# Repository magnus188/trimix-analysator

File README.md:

# Trimix Analyzer ESP32 Firmware

ESP32-P4/LVGL firmware for the Trimix Analyzer on the native-portrait Guition JC4880P443C_I_W (JC-ESP32P4-M3). It includes Wi-Fi, revision-specific HTTPS OTA, persistent settings/calibration, hardware sensor and power drivers, and a separate deterministic simulator. Physical firmware reports unavailable hardware instead of substituting simulated gas or battery readings.

**Prototype order status: HOLD.** Follow the [whole-system review](hardware/system-review/README.md) for current evidence and unresolved interfaces. No physical charging, thermal, sealing or reference-gas qualification has been completed. The accuracy targets of ±0.2 percentage points O2 and ±0.5 points He remain unproven. Charging is deliberately inhibited and J104 stays open until the cell, protection and temperature-sensing requirements are qualified.

## Project layout

The repository root is the main software workspace: firmware lives in `main/`,
with host tests in `tests/`, simulator support in `simulator/` and development
tools in `scripts/`. Mechanical and electronics files are grouped under the
[hardware overview](hardware/README.md): Fusion CAD is in `hardware/cad/`,
KiCad PCB projects are in `hardware/pcb/`, and Bambu Studio projects are in
`hardware/cad/rev04/3d-print/printing/bambu-studio/`.

## Quick Start with ESP-IDF

### Prerequisites
- [ESP-IDF v5.5.4](https://github.com/espressif/esp-idf/releases/tag/v5.5.4); `make setup-idf` installs the pinned environment
- Python 3.13
- Guition JC4880P443C_I_W: ESP32-P4 rev v1.3, 16 MB flash, 32 MB PSRAM, and ESP32-C6 coprocessor
- `g++`, CMake, pkg-config, and SDL2 development headers for full host validation

### Build and Upload
```bash
# See all common development commands
make help

# Run host-side validation
make test

# Install/check the exact ESP-IDF toolchain
make setup-idf
make doctor

# Identify whether the attached P4 is pre-v3 or v3+
make board-info PORT=/dev/cu.usbserial-110

# Build and flash; the port is required so the revision can be verified safely
make push PORT=/dev/cu.usbserial-110

# Build, flash, and monitor serial output
make push-monitor PORT=/dev/cu.usbserial-110

# Build and run the LVGL/SDL desktop simulator
make sim ZOOM=0.75
```

The first ESP32-P4 installation must be flashed over USB. An ESP32-S3 cannot
install this firmware through OTA because the chips and images are incompatible.

Run `make devices` to find likely serial ports. Firmware commands always source the pinned ESP-IDF v5.5.4 installation under `~/esp/v5.5.4/esp-idf`; an unrelated `idf.py` in `PATH` is never used. Override the installation location with `ESP_IDF_DIR=/path/to/esp-idf`.

The equivalent raw ESP-IDF commands remain available:

```bash
idf.py -B build/esp32p4-pre3 -D SDKCONFIG_DEFAULTS="sdkconfig.defaults;sdkconfig.defaults.esp32p4;sdkconfig.defaults.esp32p4.pre3" set-target esp32p4
idf.py -B build/esp32p4-pre3 build
idf.py -B build/esp32p4-pre3 -p /dev/cu.usbserial-110 flash monitor
```

## Browser Demo

The production LVGL interface can also run in a browser through WebAssembly. The browser build uses the same screens, calculator logic, and deterministic simulator services as the native SDL simulator; hardware sensors, WiFi, battery state, NVS, and OTA installation remain simulated.

### Build locally

Activate an [Emscripten SDK](https://emscripten.org/docs/getting_started/downloads.html), then run:

```bash
bash scripts/build_web_demo.sh
python3 -m http.server 8080 --directory web/build
```

Open `http://localhost:8080`. The generated site must be served over HTTP rather than opened directly from disk so the browser can load its WebAssembly module.

### Automatic GitHub Pages deployment

`.github/workflows/pages.yml` builds and deploys the demo after every push to `main`, and can also be run manually. Before the first deployment, select **GitHub Actions** under **Repository settings → Pages → Build and deployment → Source**. The project site will then be available at `https://magnus188.github.io/trimix-analysator/`.

### ESP-IDF Project Structure
```
├── CMakeLists.txt           # Main CMake configuration
├── sdkconfig.defaults       # ESP-IDF configuration defaults
├── main/                    # Main component source files
│   ├── main.cpp            # Application entry point and service startup
│   ├── services/           # WiFi, OTA, settings, battery, backlight
│   ├── sensors/            # Sensor abstraction and mock readings
│   ├── ui/                 # LVGL port, screens, styles, components
│   ├── idf_component.yml  # Component dependencies
│   └── CMakeLists.txt     # Component CMake file
├── tests/                  # Host-side C++ tests
├── scripts/                # Test and firmware size scripts
└── README.md               # This file
```

## Hardware Requirements

Use the [current electrical design](hardware/ANALYZER_DESIGN.md), [part qualification ledger](hardware/system-review/electrical/part-qualification.csv) and [main-board delivery index](hardware/system-review/electrical/main-final/README.md). These are prototype review files, not purchasing approval. Earlier enclosure/PCB snapshots preserve historical component choices.

### Controller and Display
- **ESP32-P4NRW32** application processor with 32 MB in-package PSRAM. Original pre-v3 boards are configured for their detected 16 MB flash; the v3 profile retains the 32 MB layout used by newer hardware.
- Onboard **ESP32-C6** WiFi 6/BLE coprocessor connected over SDIO.
- Native **480x800 MIPI-DSI IPS display** with ST7701 controller and GT911 capacitive touch.

### Power, Charging, and Battery
- **GCT USB4720-03-A** on a separate thin USB board, with TUSB320LAI CC detection and PI3USB9201 BC1.2 detection on the main board. USB-A-to-C and C-to-C behaviour remains subject to the documented source-current and startup tests.
- **BQ25895RTWR** 1S power-path charger, with TPS259470 overvoltage protection and TPS22950-Q1 input limiting. No USB-PD or high-voltage negotiation is provided; charging remains inhibited during commissioning.
- **Protected FMA FPML1S2P050C holder**, using its protected output. Holder/protection ratings, cell identity and NTC mounting require qualification.
- **TPS63020** configured for 5 V, with LM66100 host reverse isolation. Guition JP1 power entry remains a separate unresolved interface; do not power it through an unqualified harness.
- **TPS7A2030** regulated 3.0 V supply for the MD62.
- **LTC2954** hardware push-button shutdown plus firmware-managed normal shutdown.
- **MAX17048** 1S I2C fuel gauge.
- **2x 18650 cells in 1S2P**, owner-stated 3400 mAh each; no validated cell charge limits are inferred from capacity.
- **Normally-open momentary power button**; its final mechanical part and sealing remain unqualified.

### Sensors and Analog Front End
- Two **ADS122C04IPWR** 24-bit ADCs in TSSOP-16: U401 oxygen at 0x40 and U502 helium at 0x41. Initial profiles use 20 samples/s and the internal 2.048 V reference.
- Actual **BME280** breakout for humidity, temperature and pressure. A BMP280 cannot provide humidity.
- Retained **MD62 thermal-conductivity sensor** on regulated 3.0 V, with fixed matched bridge reference. Its helium response and compensation must be characterized with reference mixtures.
- **AO2 or R17JJ-CCR**, one installed oxygen sensor at a time. J401 and J402 have separate differential inputs; touchscreen selection and calibration identities persist independently.
- **ZE07-CO experimental module**, measuring CO rather than CO2. It is not a breathing-gas safety certification device. Its manufacturer excludes applications involving human safety; see the [CO review and manual](hardware/system-review/electrical/co-module-use-review.md). No undocumented recalibration commands are enabled. Fresh, valid chamber conditions and module warm-up are required before its reading is displayed.

### Wiring Notes
```
Signal/Rail       | Current hardware expectation
------------------|------------------------------------------------
External I2C      | GPIO28 SDA / GPIO29 SCL; managed 100 kHz sensor/power bus
Analog gas inputs | AO2/JJ differential paths and MD62 bridge into ADS122C04
HOST_3V3          | Supplied by Guition; external load margin remains unqualified
3.0 V rail        | MD62 through TPS7A2030; measure voltage at actual sensor leads
USB-C VBUS        | Protected/limited 5 V path to BQ25895
Display I2C       | GPIO7 SDA / GPIO8 SCL; separate touch/audio board bus
Onboard SD        | Slot 0: CLK43 CMD44 D0-3=39-42; LDO4 card supply
C6 SDIO           | Slot 1: CLK18 CMD19 D0-3=14-17; shared-controller arbitration
```

The [electrical/firmware/harness contract](hardware/system-review/electrical/interface-contract.md) defines logical contact mapping. The [owner photo and mechanical registration](hardware/system-review/integration-photo/README.md) place the Guition header and both USB sockets at the top and SD access on the left. Mated connector heights, cable routes and service access need their own clearance evidence. Display pins, timings and the ST7701S initialization table live in `main/board/`.

## Software Architecture

### Key Components

#### 1. Main Application (`main/main.cpp`)
- Persistent service startup
- Native display and screen initialization under the LVGL adapter lock
- Background service startup after the UI is ready

#### 2. LVGL Port (`main/ui/lvgl/lvgl_port.cpp`)
- Guition MIPI-DSI/ST7701S manual startup sequence
- Native GT911 touch registration
- Triple-buffered tear avoidance and LVGL adapter locking

#### 3. Sensor Interface (`main/sensors/sensor_interface.cpp/h`)
- Abstracted sensor reading functions
- Separate physical acquisition and deterministic simulator backends
- Persistent sensor selection and versioned calibration; stale, clipped and faulty samples are rejected

#### 4. Screen Management (`main/ui/screens/screen_manager.cpp/h`)
- LVGL-based UI screens
- Navigation between screens
- Settings, WiFi, update, and dive planner screens

#### 5. Services (`main/services/`)
- WiFi scanning/connection and saved credentials
- OTA update checks and firmware installation
- Settings, battery status, and backlight control
- Analysis history, persistent cylinder profiles, and export-ready gas label payloads

#### 6. Board Support
- In-tree Guition JC4880P443 display, backlight, and touch layer
- Separate pre-v3 and v3+ ESP32-P4 build profiles
- Native backlight, display, touch, and onboard ESP32-C6 integration

## Display Configuration

### ESP32-P4 Display
- **Panel**: 480x800 native portrait
- **Framework**: LVGL
- **Touch**: Capacitive (GT911)

### Screens

1. **Home Screen**
   - Main menu with navigation buttons
   - System status display
   - Version information

2. **Analyse Screen**
   - Gas analysis panel with physical and separately identified simulator sources
   - O2, He, experimental CO, environmental readings, stability, trend chart, planned depth, MOD, density, gas-use mode and averaged capture controls
   - Captures require stable samples and save an averaged analysis result to history
   - Stable averaged readings can update the selected cylinder profile and prepare an export-ready label payload

3. **Dive Planner Screen**
   - Gas planning calculator views
   - Partial-pressure top-up calculator for O2, helium, and air additions
   - Production calculator logic covered by host tests

4. **History Screen**
   - Captured analysis records with gas-use mode, mix fractions, CO, planned depth, MOD, density and advisory state; legacy CO2 fields remain distinct and are not relabelled as CO

5. **Cylinder Profiles Screen**
   - Persistent cylinder slots with selected cylinder, recheck state, stored mix, gas-use mode, planned depth, and label preview
   - Label text and CSV payloads are generated in firmware so later WiFi, QR, BLE, or phone handoff export can reuse the same data model

6. **Settings Screen**
   - Device settings navigation
   - Cylinder profiles, WiFi, software update, safety settings, calibration, and device information entrypoints

7. **WiFi Screen**
   - Network scanning, connection, password modal, and disconnect controls

8. **Software Update Screen**
   - GitHub release check and OTA install flow

9. **Calibrate Sensors Screen**
   - Guided known-gas oxygen and helium calibration with stability/fault checks and separate AO2/JJ/He records; failed saves retain the previous calibration

10. **Safety Settings Screen**
   - User-configured PPO2, density, and CO2 advisory limits used by Analyse

11. **Device Screen**
   - Device information and configuration controls

## Building and Flashing

### Prerequisites
- **ESP-IDF v5.5.4** installed with `make setup-idf`
- **ESP32-P4** toolchain and Python 3.13
- **Host validation tools**: `g++`, CMake, pkg-config, SDL2 development headers
- USB-C cable for programming

### Build Steps
```bash
# Inspect the attached chip and select the safe image family
make board-info PORT=/dev/cu.usbserial-110

# Run host tests
./scripts/run_tests.sh

# Build both incompatible P4 revision profiles
make build-all

# Validate firmware size against partitions.csv
make size-check P4_REV=pre3
make size-check P4_REV=v3

# Flash to device
make push PORT=/dev/cu.usbserial-110

# Monitor output
make monitor PORT=/dev/cu.usbserial-110
```

### Dependencies
The project uses ESP-IDF component manager for dependencies (defined in `main/idf_component.yml`):
- `lvgl/lvgl` 9.4.0 - Graphics library
- `espressif/esp_lcd_touch_gt911` 1.2.x - capacitive touch controller
- `espressif/esp_lvgl_adapter` 0.1.4 - task, input, and tear-safe display integration
- `espressif/esp_wifi_remote` 1.6.0 and `espressif/esp_hosted` 2.12.9 - onboard C6 networking

Dependencies are automatically downloaded during the build process.

## Sensor Hardware and Calibration Status

Physical firmware implements ADS122C04 acquisition, environmental and power monitoring, sensor selection and calibration persistence. Host tests exercise faults and state transitions; they do not establish actual sensor performance, wiring or charging behaviour. The simulator remains explicitly identified and does not substitute readings in physical firmware.

AO2, JJ-CCR and helium have separate records. Replacing a sensor requires calibration. Helium corrections must come from measured reference mixtures and held-out validation, including environmental and oxygen cross-effects. Historical/simulated CO2 fields remain distinct; this build has no installed CO2 measurement module. See the [software review](hardware/system-review/software/README.md).

## Performance Characteristics

### Display Pipeline
- **Panel**: native 480x800 RGB565 over two-lane MIPI-DSI
- **Tear avoidance**: three full panel framebuffers with partial LVGL rendering
- **LVGL refresh period**: 15 ms
- **Rotation**: none; pixels and touch coordinates stay in native portrait orientation

### Power Consumption
Whole-device active, idle, charging and hardware-off consumption remains unmeasured. Qualify backlight, radio, SD writes, heaters, converters and cable losses together; a display-only typical value is not a system budget. See the [bench equipment and test plan](hardware/system-review/lab-equipment.md).

## Differences from Original

### Enhanced Features
1. **480x800 portrait touch display**
2. **Capacitive touch**
3. **Tear-safe MIPI-DSI output** with no full-frame software rotation
4. **Software-defined sensor selection and calibration**
5. **Versioned OTA and persistent storage**; boot-time and power comparisons remain unmeasured

### Current Limitations
1. Physical fit, source protection, cell charging, thermal behaviour and gas accuracy remain unqualified; PCB order readiness is on hold.
2. Simulator streams support repeatable UI/logic tests; they are not physical measurement evidence.
3. Settings, calibration and recent history remain in NVS. [Optional onboard SD logging](hardware/system-review/software/sd-card/README.md) automatically records analysis/calibration sessions, raw samples and events. Device Settings provides status, safe eject and retry. Digital tests pass; actual card operation, power loss and simultaneous Wi-Fi use remain untested. Absent or faulty media leaves local analysis available.

## Development Notes

### Code Organization
- Sensor interface abstraction allows host tests and later hardware drivers.
- Modular screen design keeps LVGL screens separated by workflow.
- Services isolate WiFi, OTA, settings, battery, and backlight behavior.
- Board-level display and touch details are implemented in `main/board/guition_jc4880p443.c`.

### Testing Strategy
- `./scripts/run_tests.sh` runs static safety checks, production gas calculator tests, version consistency tests, and the host LVGL simulator smoke test when SDL2 is available.
- `./scripts/check_firmware_size.sh` validates the built app binary against the configured factory/OTA app partition.
- Hardware acceptance covers touch corners and drag axes, 100 navigation operations, a one-hour active UI/WiFi soak, an eight-hour idle soak, and two consecutive OTA upgrades.

## Troubleshooting

### Common Issues

1. **Display not working**
   - Verify the qualified 5 V power entry and source-current budget; follow the staged first-power procedure
   - Verify display cable connections
   - Confirm the PCB/module markings read `Guition JC4880P443` / `JC-ESP32P4-M3`
   - Confirm `make board-info` and the selected build profile agree

2. **Touch not responding**
   - Check the GT911 I2C bus on GPIO7 SDA / GPIO8 SCL
   - Confirm the board is physically mounted in native portrait orientation
   - Ensure proper grounding

3. **Sensors not reading**
   - Check I2C bus connections
   - Check device identities and bus errors in firmware diagnostics; use the documented I2C pin/address map
   - Check power supply to sensors

4. **Build errors**
   - Run `make doctor` and confirm ESP-IDF v5.5.4 with Python 3.13
   - Run `make clean`, then rebuild the correct P4 revision profile
   - Check that Git dependencies and `dependencies.lock` are available

### Debug Commands
```bash
# Read firmware diagnostics; no generic I2C-scan console is assumed
idf.py monitor

# Memory usage
idf.py size

# Real-time monitoring
idf.py monitor --decode-crashes
```

## Contributing

When adding new features:
1. Follow ESP-IDF coding standards
2. Keep display/touch changes inside the board-port boundary; do not add manual rotation
3. Add screen navigation in `main/ui/screens/screen_manager.cpp`
4. Test with both real and mock sensors
5. Update documentation

## License

Same as original Trimix Analyzer project.

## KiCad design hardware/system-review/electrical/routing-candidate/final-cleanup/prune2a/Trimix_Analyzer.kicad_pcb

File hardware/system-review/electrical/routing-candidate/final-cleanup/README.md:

# Completed main routing review checkpoint

The frozen main source is `frozen-bundle/hardware/pcb/analyzer/Trimix_Analyzer.kicad_pcb`, SHA256 `9f274fdf198f1bcb871a4fc360e76693f8a5b048553e6a02998141737956514f`. Native KiCad reports zero violations, zero opens and zero schematic mismatches. It has 169 footprints, 2280 track segments and 301 routed vias. **Manufacturing/physical acceptance remains on HOLD.**

The [geometry manifest](frozen-bundle/review/geometry-handoff-manifest.json) binds PCB, XML, STEP and all 153 maximum-envelope rows. The STEP uses normal pad thickness and unit-scale purchased-part reference models. U110/L201/L701 model files are absent from the installed KiCad model library; their explicit maximum envelopes remain mandatory. No absent or generic model is treated as a dimensional pass.

- [Root power/ground review](root-review/final-power-ground-review.json): all 29 critical conductor witnesses retained, continuous In1, 105 In1 and 21 In2 anchors retained, every In2 region anchored.
- [Aggregate consolidation delta](aggregate-consolidation-delta.json): 519 structural checks; no part, pad, pose or model change during cleanup. The accepted C708 ordinary-via dogbone and dead-copper cleanup are explicit. All 195 physical pad-connectivity partitions are conserved. `prune2/REJECTED.txt` retains the negative control that caught a mistakenly removed live midpoint connection; the accepted source restored it and trimmed only its dead extension.
- [Native routing audit](frozen-bundle/review/routing-audit.json): 12 checks pass. [Via/paste interface audit](frozen-bundle/review/via-assembly-audit.json): all 301 routed vias checked; only the exact three VIPPO sites are permitted in populated SMT paste.
- [Root ERC/firmware contract review](root-review/final-contract-erc-review.json): one precisely reviewed TI-permitted LM66100 ST-ground ERC error, no unexpected ERC findings; all 70 logical firmware-contract checks pass. `source-validation/electrical/electrical-audit.json` has 217 passing assertions; `source-validation/audit-faults/audit-fault-tests.json` accepts the baseline and rejects all 12 injected wiring/value faults.
- [CAM input manifest](frozen-bundle/review/cam-input-manifest.json) binds the unmodified Gerbers, drills, all-component CPL and population ledgers. Independent final CAM results are under `../../main-final-independent/final-9f274fdf/`.

`frozen-bundle/cam/assembly-reference-map.csv` lists every reference, value, MPN, side and position. Separate lists contain 24 factory components, 121 manual components, 6 DNPs and 18 PCB/harness features. `marking-legend.csv` identifies the 146 printed references. The 23 dense assembly-only references have [four locator sheets](assembly-drawings/assembly-only-locators-1.svg); subsequent pages use suffixes 2–4. These show selected pads in blue and use explicit top-view coordinates for both sides. They complement actual CAM silk and the CSV. Raw native Fab exports are retained as diagnostics; their overlapping value text is not claimed to be the clear assembly drawing.

The [factory stencil supplement](factory-stencil/derivation-receipt.json) removes only non-factory paste apertures from a derived copy. The original routed source and full-board paste remain frozen for comparison. The [27-hole process map](fill-cap-process/README.md) requires resin fill and copper cap for all 24 package thermal bores plus 3 signal VIPPO. A quotation must establish drill classification, flatness, stencil thickness/apertures, void/coverage acceptance and double-sided reflow. Neither paste geometry nor a generic capability page proves assembled quality.

Final source-bound enclosure integration, actual sensor/host/harness mating and power entry, cell/NTC identity, USB transient/current/standby/true-off recovery, thermal, EMC, gas and calibration qualification remain separate acceptance gates. No physical test or purchase has been performed.

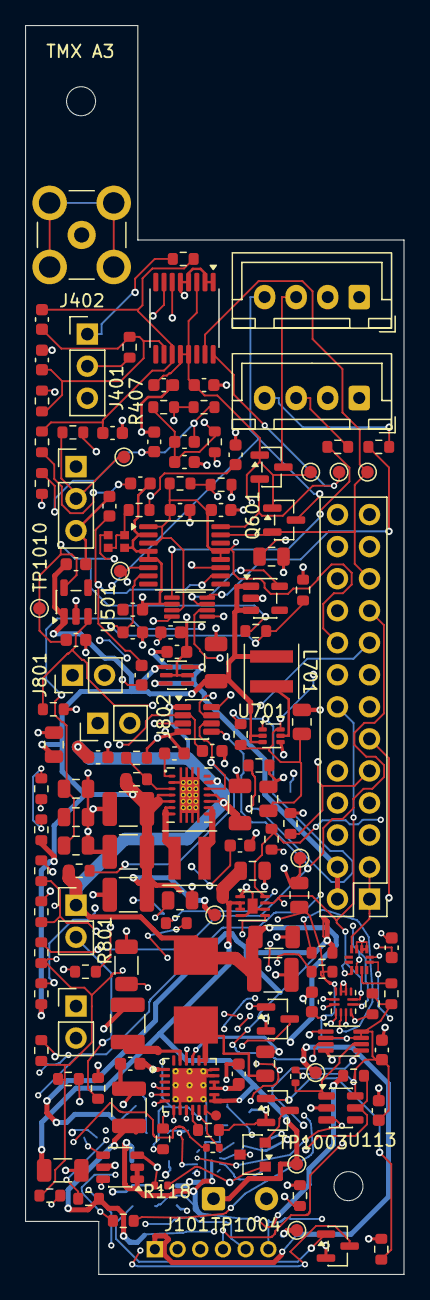
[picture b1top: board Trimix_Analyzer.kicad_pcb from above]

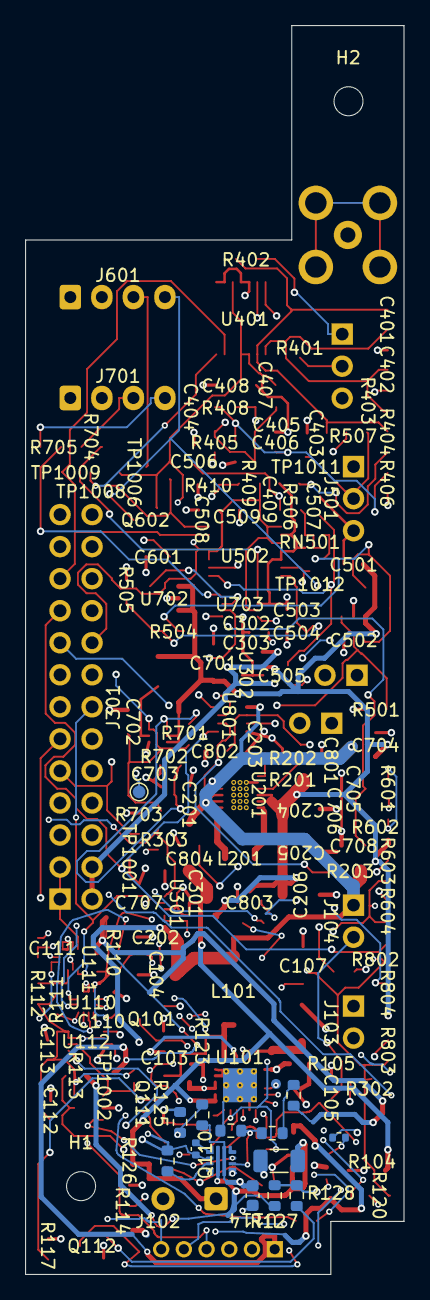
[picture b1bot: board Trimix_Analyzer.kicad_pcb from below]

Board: 4 copper layers, 30.0 x 99.0 mm, 169 parts (15 on the bottom side), 86 nets.

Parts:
C101, C401, C404, C408, C409, C505, C509, C804: 1u / 16V X7R / 10%; C_0603_1608Metric
C102, C104, C105, C204, C205, C206: 22u / 16V X7R / 20%; C_1210_3225Metric
C103: 47n / 50V X7R / 10%; C_0805_2012Metric
C106, C107, C201, C202, C701: 22u / 25V X5R / 20%; C_1206_3216Metric
C108, C302, C303, C501, C502: 4.7u / 16V X5R / 10%; C_0603_1608Metric
C110, C111, C112, C113, C203, C407, C504, C508, C801, C802: 100n / 50V X7R / 10%; C_0603_1608Metric
C114: 4.7u / 25V X7R / 10%; C_1206_3216Metric
C115: 100n / 50V X7R; C_0603_1608Metric
C116: 3.3n / 50V C0G / 5%; C_0402_1005Metric
C301, C707, C708: 100n / 50V X7R / 10%; C_0805_2012Metric
C402, C403, C405, C406, C506, C507: 10n / 50V X7R / 10%; C_0603_1608Metric
C503: 10n / 50V X7R / 10% / DNP; C_0603_1608Metric
C601, C704, C705: 1u / 25V X7R / 10%; C_0805_2012Metric
C702, C703: 22u / 16V X5R / 20%; C_0805_2012Metric
C706: 10n / 50V X7R / 10% / DNP; C_0805_2012Metric
C803: 33n / 50V X7R / 10%; C_0805_2012Metric
H1, H2: M2 NPTH 2.30; Mechanical_M2_NPTH_2.30mm
J101: USB HARNESS: 5V/GND/CC1/CC2/D+/D-; USB_Harness_6P_P1.8mm
J102: PACK PIGTAIL; Battery_Pigtail_2x22AWG_P4.2_D1.00_Pad1.85
J103: PACK NTC: 103AT-2; PinHeader_1x02_P2.54mm_Vertical
J104: ARM: OPEN; PinHeader_1x02_P2.54mm_Vertical
J301: GUITION JP1 / 2x13; Samtec_HTSW-113-07-L-D-007_P2.54mm_Key7
J401: AO2 / 3-pin cable; PinHeader_1x03_P2.54mm_Vertical
J402: SMB male-centre / Amphenol142138; SMB_Amphenol_142138
J501: MD62 cable / <=30 cm; PinHeader_1x03_P2.54mm_Vertical
J601: BME280 harness; JST_XH_B4B-XH-A_1x04_P2.50mm_Vertical
J701: ZE07-CO harness; JST_XH_B4B-XH-A_1x04_P2.50mm_Vertical
J801: POWER BUTTON / 1NO; PinHeader_1x02_P2.54mm_Vertical
J802: BUTTON LED +/-; PinHeader_1x02_P2.54mm_Vertical
L101: 1u / 74437349010; L_Wurth_74437349010_7050
L201: 1.5u / XGL4030-152MEC; L_Coilcraft_XGL4030
L701: 1u / XGL4020-102MEC; L_Coilcraft_XGL4020
Q101: 2N7002; SOT-23
Q110: DMN2056U-7; DMN2056U_SOT23_Diodes_Recommended
Q111, Q112: DMN2056U-7; SOT-23
Q601, Q602: BSS138; SOT-23
R101: 5.23k 1%; R_0402_1005Metric
R102: 30.1k 1%; R_0603_1608Metric
R103: 300R / 1% / supported ILIM range; R_0603_1608Metric
R104, R105, R203, R501, R703, R803: 100k; R_0603_1608Metric
R107, R301, R802: 10k; R_0603_1608Metric
R110: 887k / 1%; R_0603_1608Metric
R111: 33k / 1%; R_0603_1608Metric
R112, R120, R127: 10k / 1%; R_0603_1608Metric
R113: 97.6k / 0.1%; R_0603_1608Metric
R114, R409, R410, R504, R505: 10k / 0.1%; R_0603_1608Metric
R115: 10k / 0.1%; R_0402_1005Metric
R116: 1k / 0.1%; R_0603_1608Metric
R117, R128: 100k / 1%; R_0603_1608Metric
R118: 100k / 0.1%; R_0402_1005Metric
R119: 19.1k / 0.1%; R_0402_1005Metric
R121: 34k / 0.1% / 10ppm; R_0603_1608Metric
R122: 649R / 0.1% / 10ppm; R_0603_1608Metric
R123: 10k / 0.1% / 10ppm; R_0603_1608Metric
R124: 21.5k / 0.1% / 25ppm; R_0603_1608Metric
R125: 10k / 0.1% / 25ppm; R_0603_1608Metric
R126: 1.65k / 0.1%; R_0603_1608Metric
R201: 1.62M 1%; R_0603_1608Metric
R202: 180k 1%; R_0603_1608Metric
R302, R303: 4.7k / FIT; R_0603_1608Metric
R401, R402, R405, R406: 100R / 0.1%; R_0603_1608Metric
R403, R404, R407, R408: 1M / 1%; R_0603_1608Metric
R506, R507: 680R / 0.1%; R_0603_1608Metric
R601: 0R / fit: 3.3 V; R_0603_1608Metric
R602: 0R / DNP: 5 V option; R_0603_1608Metric
R603, R604: 4.7k / DNP; R_0603_1608Metric
R701: 787k / 0.1%; R_0603_1608Metric
R702: 100k / 0.1%; R_0603_1608Metric
R704, R705: 100R; R_0603_1608Metric
R801: 5.1k; R_0603_1608Metric
R804: 1k / DNP; R_0603_1608Metric
RN501: 2x2k / 1:1 matched; Vishay_ACAS0606_AT_IEC
TP1001: GND; TestPoint_Pad_D1.0mm
TP1002: USB_5V; TestPoint_Pad_D1.0mm
TP1003: PACK_P; TestPoint_Pad_D1.0mm
TP1004: VSYS; TestPoint_Pad_D1.0mm
TP1005: VOUT_5V; TestPoint_Pad_D1.0mm
TP1006: HOST_3V3; TestPoint_Pad_D1.0mm
TP1007: POWER_EN; TestPoint_Pad_D1.0mm
TP1008: I2C_SCL; TestPoint_Pad_D1.0mm
TP1009: I2C_SDA; TestPoint_Pad_D1.0mm
TP1010: HE_3V0; TestPoint_Pad_D1.0mm
TP1011: HE_SENSE; TestPoint_Pad_D1.0mm
TP1012: O2_VMID; TestPoint_Pad_D1.0mm
TP1013: CHG_STAT_N; TestPoint_Pad_D0.8mm
TP1014: QON SERVICE; TestPoint_Pad_D0.8mm
U101: BQ25895RTWR; TI_RTW24_4x4_ThermalVias_ServicePad
U110: TUSB320LAIRWBR; Texas_X2QFN-12_1.6x1.6mm_P0.4mm
U111: PI3USB9201ZTAEX; PI3USB9201_UQFN2020_12_TypeC
U112: SN74AUP1G74DCUR; VSSOP-8_2.3x2mm_P0.5mm
U113: TPS3808G01DBVR; SOT-23-6
U114: TPS22950CQDDCRQ1; TI_DDC0006A
U115: TPS259470ARPWR; TI_RPW0010A
U201: TPS63020DSJR; TI_DSJ_14
U301: MAX17048G+; TDFN-8-1EP_2x2mm_P0.5mm_EP0.8x1.2mm
U302: LM66100DCKR; SOT-363_SC-70-6
U401, U502: ADS122C04IPWR; TSSOP-16_4.4x5mm_P0.65mm
U501, U702: TPS7A2030PDBVR; SOT-23-5
U701: TPS61023DRLR; SOT-563
U703: TXU0202DCUR; TI_DCU8_CompactSilk
U801: LTC2954CTS8-1; TSOT-23-8

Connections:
/01 CHARGING + BATTERY/BQ_BTST: C103.2, U101.21 (BTST)
/01 CHARGING + BATTERY/BQ_PMID: C102.1, U101.23 (PMID)
/01 CHARGING + BATTERY/BQ_QON_N: TP1014.1, U101.12 (~QON)
/01 CHARGING + BATTERY/BQ_REGN: C107.1, R101.1, U101.22 (REGN)
/01 CHARGING + BATTERY/BQ_SW: C103.1, L101.1, U101.19 (SW), U101.20 (SW)
/01 CHARGING + BATTERY/CHG_CE_N: Q101.3 (D), R104.2, U101.9 (~CE)
/01 CHARGING + BATTERY/CHG_STAT_N: TP1013.1, U101.4 (STAT)
/01 CHARGING + BATTERY/PACK_TS: J103.1, R101.2, R102.1, U101.11 (TS)
/02 SWITCHED 5 V/TPS_FB: R201.2, R202.1, U201.3 (FB)
/02 SWITCHED 5 V/TPS_VINA: C203.1, U201.1 (VINA)
BME_SCL: J601.3 (SCL), Q601.3 (D), R603.2
BME_SDA: J601.4 (SDA), Q602.3 (D), R604.2
BME_VIN: C601.1, J601.1 (VIN), R601.2, R602.2, R603.1, R604.1
BQ_ILIM: R103.1, U101.10 (ILIM)
BUTTON_LED_A: J802.1, R804.2
CHARGE_ARM: J104.2 (B), Q101.1 (G), R105.1
CHG_INT_N: J301.13, Q112.3 (D), R107.2, U101.7 (~INT)
CO_5V28: C702.1, C703.1, J701.1 (5.28V), R701.1, U701.6 (VOUT)
CO_FB: R701.2, R702.1, U701.1 (FB)
CO_LOGIC_3V0: C705.1, C708.1, U702.5 (OUT), U703.7 (VCCB)
CO_RX_3V0: R705.1, U703.8 (B1Y)
CO_RX_CABLE: J701.4 (CO_RX), R705.2
CO_SW: L701.2, U701.5 (SW)
CO_TX_3V0: R704.1, U703.1 (B2)
CO_TX_CABLE: J701.3 (CO_TX), R704.2
CO_UART_EN: J301.9, R703.1, U703.6 (OE)
CO_UART_RX: J301.10, U703.4 (A2Y)
CO_UART_TX: J301.12, U703.5 (A1)
GAUGE_ALERT_N: R301.2, U301.5 (ALRT)
GND: C101.2, C102.2, C104.2, C105.2, C106.2, C107.2, C108.2, C110.2, C111.2, C112.2, C113.2, C114.2, C115.2, C116.2, C201.2, C202.2, C203.2, C204.2, C205.2, C206.2, C301.2, C302.2, C303.2, C402.2, C403.2, C405.2, C406.2, C407.2, C408.2, C409.2, C501.2, C502.2, C503.2, C504.2, C506.2, C507.2, C508.2, C509.2, C601.2, C701.2, C702.2, C703.2, C704.2, C705.2, C706.2, C707.2, C708.2, C801.2, C802.2, C803.2, C804.2, J101.2, J102.2, J103.2, J301.5, J301.6, J301.16, J501.3, J601.2 (GND), J701.2 (GND), J801.2, J802.2, Q101.2 (S), Q111.2 (S), Q112.2 (S), R102.2, R103.2, R105.2, R114.2, R117.2, R118.2, R119.2, R123.2, R125.2, R126.2, R127.2, R128.2, R202.2, R410.2, R501.2, R505.2, R702.2, R703.2, RN501.3 (R2.2), TP1001.1 (1_1), U101.8 (OTG), U101.17 (PGND), U101.18 (PGND), U101.25 (PGND), U110.3 (PORT), U110.5 (ADDR), U110.10 (GND), U110.11 (EN_N), U111.9 (GND), U111.10 (ADDR), U111.11 (ENB), U112.4 (GND), U113.2 (GND), U114.3 (GND), U115.8 (GND), U201.2 (GND), U201.15 (PGND/EP), U301.1 (CTG), U301.4 (GND), U301.6 (QSTRT), U301.9 (EP), U302.2 (GND), U302.5 (ST), U401.1 (A0), U401.2 (A1), U401.4 (DGND), U401.5 (AVSS), U501.2 (GND), U502.2 (A1), U502.4 (DGND), U502.5 (AVSS), U701.4 (GND), U702.2 (GND), U703.2 (GND), U801.4 (GND)
HE_3V0: C502.1, J501.1, R504.1, RN501.1 (R1.1), TP1010.1 (1_1), U501.5 (OUT)
HE_AIN_N: C505.2, C507.1, R507.2, U502.10 (AIN1)
HE_AIN_P: C505.1, C506.1, R506.2, U502.11 (AIN0)
HE_ENABLE: J301.17, R501.1, U501.3 (EN)
HE_EXC_DIV: C504.1, R504.2, R505.1, U502.7 (AIN2)
HE_REF: R506.1, RN501.2 (R2.1), RN501.4 (R1.2)
HE_SENSE: J501.2, R507.1, TP1011.1 (1_1)
HOST_3V3: C110.1, C111.1, C112.1, C113.1, C407.1, C408.1, C508.1, C509.1, C707.1, J301.1, J301.3, J301.18, Q601.1 (G), Q602.1 (G), R107.1, R111.1, R112.1, R115.1, R120.1, R301.1, R302.1, R303.1, R409.1, R601.1, R802.1, R803.1, TP1006.1 (1_1), U110.12 (VDD), U111.12 (VDD), U112.2 (D), U112.7 (PRE_N), U112.8 (VCC), U113.6 (VDD), U401.3 (~RESET), U401.12 (AVDD), U401.13 (DVDD), U502.1 (A0), U502.3 (~RESET), U502.12 (AVDD), U502.13 (DVDD), U703.3 (VCCA)
HOST_5V: C303.1, J301.2, J301.4, U302.3 (CE), U302.6 (VOUT)
I2C_SCL: J301.14, Q601.2 (S), R302.2, TP1008.1 (1_1), U101.5 (SCL), U110.8 (SCL), U111.3 (SCL), U301.7 (SCL), U401.16 (SCL), U502.16 (SCL)
I2C_SDA: J301.21, Q602.2 (S), R303.2, TP1009.1 (1_1), U101.6 (SDA), U110.7 (SDA), U111.4 (SDA), U301.8 (SDA), U401.15 (SDA), U502.15 (SDA)
unnamed: J801.1, R801.1
unnamed: L201.1, U201.8 (L1), U201.9 (L1)
unnamed: L201.2, U201.6 (L2), U201.7 (L2)
unnamed: C803.1, U801.3 (ONT)
unnamed: C804.1, U801.7 (PDT)
O2_A_AIN_N: C401.1, C402.1, R401.2, R403.1, U401.10 (AIN1)
O2_A_AIN_P: C401.2, C403.1, R402.2, R404.2, U401.11 (AIN0)
O2_A_RAW_N: J401.2, R401.1
O2_A_RAW_P: J401.1, R402.1
O2_B_AIN_N: C404.1, C405.1, R405.2, R407.1, U401.6 (AIN3)
O2_B_AIN_P: C404.2, C406.1, R406.2, R408.2, U401.7 (AIN2)
O2_B_RAW_N: J402.2 (Ext), R405.1
O2_B_RAW_P: J402.1 (In), R406.1
O2_VMID: C409.1, R403.2, R404.1, R407.2, R408.1, R409.2, R410.1, TP1012.1 (1_1), U502.6 (AIN3)
PACK_P: C106.1, C301.1, J102.1, TP1003.1 (1_1), U101.13 (BAT), U101.14 (BAT), U301.2 (CELL), U301.3 (VDD)
PB_FILTERED_N: C802.1, R801.2, U801.2 (~PB)
POWER_EN: R203.2, TP1007.1 (1_1), U201.12 (EN), U801.6 (EN)
POWER_INT_N: J301.19, R802.2, U801.5 (~INT)
POWER_KILL_N: J301.8, R803.2, U801.8 (~KILL)
USB_5V: C115.1, J101.1, R110.1, R121.1, R124.1, TP1002.1 (1_1), U115.5 (IN)
USB_BC_INT_N: R112.2, U111.5 (INTB)
USB_CC1: J101.3, U110.1 (CC1)
USB_CC2: J101.4, U110.2 (CC2)
USB_CC_INT_N: R111.2, U110.6 (INT_N), U113.3 (MR), U115.3 (AUXOFF)
USB_CHG_5V: C101.1, U101.1 (VBUS), U114.5 (VOUT)
USB_D_M: J101.6, U111.7 (D-)
USB_D_P: J101.5, U111.8 (D+)
USB_ILIM_AUTH: J301.11, Q111.1 (G), R117.1, U112.1 (CLK)
USB_ILIM_BRANCH: Q110.3 (D), R116.2
USB_ILIM_SERIES: Q110.2 (S), Q111.3 (D)
USB_LIMIT_FAULT_N: R120.2, U114.6 (FLT)
USB_LIMIT_SET: R116.1, R119.1, U114.4 (ILIM)
USB_OVP_5V: C114.1, R113.1, R127.1, U114.1 (ON), U114.2 (VIN), U115.6 (OUT)
USB_OVP_DVDT: C116.1, U115.7 (DVDT)
USB_OVP_ILM: R126.1, U115.9 (ILM)
USB_OVP_SET: R122.2, R123.1, U115.2 (OVLO)
USB_OVP_UPPER: R121.2, R122.1
USB_OVP_UVLO: R124.2, R125.1, U115.1 (EN/UVLO)
USB_PERMISSION_CLR_N: R115.2, U112.6 (CLR_N), U113.1 (RESET)
USB_PERMISSION_Q: Q110.1 (G), R118.1, U112.5 (Q)
USB_PERMISSION_Q_N: Q112.1 (G), R128.1, U112.3 (Q_N)
USB_VBUS_DET: R110.2, U110.4 (VBUS_DET)
USB_VBUS_SENSE: R113.2, R114.1, U113.5 (SENSE)
VOUT_5V: C204.1, C205.1, C206.1, C302.1, C501.1, C701.1, C704.1, L701.1, R201.1, R602.1, R804.1, TP1005.1 (1_1), U201.4 (VOUT), U201.5 (VOUT), U302.1 (VIN), U501.1 (IN), U701.2 (EN), U701.3 (VIN), U702.1 (IN), U702.3 (EN)
VSYS: C104.1, C105.1, C108.1, C201.1, C202.1, C801.1, J104.1 (A), L101.2, R104.1, R203.1, TP1004.1 (1_1), U101.15 (SYS), U101.16 (SYS), U201.10 (VIN), U201.11 (VIN), U201.13 (PS/SYNC), U801.1 (VIN)

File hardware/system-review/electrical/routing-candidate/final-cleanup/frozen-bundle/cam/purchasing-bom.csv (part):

Reference,Value,Manufacturer,MPN,Quantity,Population_quantity,Category,Footprint,Side,PCB_X_mm,PCB_Y_mm,Rotation_deg,Assembly_note,Native_exclude_from_BOM,Native_exclude_from_CPL
C101,1u / 16V X7R / 10%,KEMET / YAGEO,C0603C105K4RACTU,1,1,manual,C_0603_1608Metric,top,8.3,82.3,180.0,"manual assembly after factory inspection, using iron/hot air and microscope",False,False
C102,22u / 16V X7R / 20%,TDK,C3225X7R1C226M250AC,1,1,manual,C_1210_3225Metric,top,8.1,79.1,90.0,"manual assembly after factory inspection, using iron/hot air and microscope",False,False
C103,47n / 50V X7R / 10%,KEMET / YAGEO,C0805C473K5RACTU,1,1,manual,C_0805_2012Metric,top,19.0,82.3,90.0,"manual assembly after factory inspection, using iron/hot air and microscope",False,False
C104,22u / 16V X7R / 20%,TDK,C3225X7R1C226M250AC,1,1,manual,C_1210_3225Metric,top,19.6,75.25,0.0,"manual assembly after factory inspection, using iron/hot air and microscope",False,False
C105,22u / 16V X7R / 20%,TDK,C3225X7R1C226M250AC,1,1,manual,C_1210_3225Metric,top,8.199999,85.75,90.0,"manual assembly after factory inspection, using iron/hot air and microscope",False,False
C106,22u / 25V X5R / 20%,TDK,C3216X5R1E226M160AB,1,1,manual,C_1206_3216Metric,top,2.95,90.75,0.0,"manual assembly after factory inspection, using iron/hot air and microscope",False,False
C107,22u / 25V X5R / 20%,TDK,C3216X5R1E226M160AB,1,1,manual,C_1206_3216Metric,top,8.0,74.5,90.0,"manual assembly after factory inspection, using iron/hot air and microscope",False,False
C108,4.7u / 16V X5R / 10%,TDK,C1608X5R1C475K080AC,1,1,manual,C_0603_1608Metric,top,16.9,83.1,90.0,"manual assembly after factory inspection, using iron/hot air and microscope",False,False
C110,100n / 50V X7R / 10%,TDK,C1608X7R1H104K080AA,1,1,manual,C_0603_1608Metric,top,22.7,77.4,90.0,"manual assembly after factory inspection, using iron/hot air and microscope",False,False
C111,100n / 50V X7R / 10%,TDK,C1608X7R1H104K080AA,1,1,manual,C_0603_1608Metric,top,29.025,73.1,90.0,"manual assembly after factory inspection, using iron/hot air and microscope",False,False
C112,100n / 50V X7R / 10%,TDK,C1608X7R1H104K080AA,1,1,manual,C_0603_1608Metric,top,28.0,86.0,90.0,"manual assembly after factory inspection, using iron/hot air and microscope",False,False
C113,100n / 50V X7R / 10%,TDK,C1608X7R1H104K080AA,1,1,manual,C_0603_1608Metric,top,28.25,81.2,90.0,"manual assembly after factory inspection, using iron/hot air and microscope",False,False
C114,4.7u / 25V X7R / 10%,TDK,C3216X7R1E475K160AC,1,1,manual,C_1206_3216Metric,bottom,9.9,90.0,0.0,"manual assembly after factory inspection, using iron/hot air and microscope",False,False
C115,100n / 50V X7R,TDK,C1608X7R1H104K080AA,1,1,manual,C_0603_1608Metric,bottom,12.0,92.75,-90.0,"manual assembly after factory inspection, using iron/hot air and microscope",False,False
C116,3.3n / 50V C0G / 5%,Murata,GRM1555C1H332JE01D,1,1,factory,C_0402_1005Metric,bottom,16.5,89.05,-90.0,Factory reflow for true 0402 part; 3.3nF C0G slew timing function unchanged; exact BOM/CPL quote required; quoted factory SMT placement/reflow and joint inspection required,False,False
C201,22u / 25V X5R / 20%,TDK,C3216X5R1E226M160AB,1,1,manual,C_1206_3216Metric,top,17.0,61.75,90.0,"manual assembly after factory inspection, using iron/hot air and microscope",False,False
C202,22u / 25V X5R / 20%,TDK,C3216X5R1E226M160AB,1,1,manual,C_1206_3216Metric,top,19.7,72.25,0.0,"manual assembly after factory inspection, using iron/hot air and microscope",False,False
C203,100n / 50V X7R / 10%,TDK,C1608X7R1H104K080AA,1,1,manual,C_0603_1608Metric,top,11.8,57.7,0.0,"manual assembly after factory inspection, using iron/hot air and microscope",False,False
C204,22u / 16V X7R / 20%,TDK,C3225X7R1C226M250AC,1,1,manual,C_1210_3225Metric,top,8.15,62.1,180.0,"manual assembly after factory inspection, using iron/hot air and microscope",False,False
C205,22u / 16V X7R / 20%,TDK,C3225X7R1C226M250AC,1,1,manual,C_1210_3225Metric,top,8.15,65.5,180.0,"manual assembly after factory inspection, using iron/hot air and microscope",False,False
C206,22u / 16V X7R / 20%,TDK,C3225X7R1C226M250AC,1,1,manual,C_1210_3225Metric,top,8.15,68.9,180.0,"manual assembly after factory inspection, using iron/hot air and microscope",False,False
C301,100n / 50V X7R / 10%,KEMET / YAGEO,C0805C104K5RACTU,1,1,manual,C_0805_2012Metric,top,18.0,67.0,0.0,"manual assembly after factory inspection, using iron/hot air and microscope",False,False
C302,4.7u / 16V X5R / 10%,TDK,C1608X5R1C475K080AC,1,1,manual,C_0603_1608Metric,top,11.5,48.1,0.0,"manual assembly after factory inspection, using iron/hot air and microscope",False,False
C303,4.7u / 16V X5R / 10%,TDK,C1608X5R1C475K080AC,1,1,manual,C_0603_1608Metric,top,12.0,49.65,0.0,"manual assembly after factory inspection, using iron/hot air and microscope",False,False
C401,1u / 16V X7R / 10%,KEMET / YAGEO,C0603C105K4RACTU,1,1,manual,C_0603_1608Metric,top,1.299999,23.3,90.0,"manual assembly after factory inspection, using iron/hot air and microscope",False,False
C402,10n / 50V X7R / 10%,TDK,C1608X7R1H103K080AA,1,1,manual,C_0603_1608Metric,top,1.299999,26.51,90.0,"manual assembly after factory inspection, using iron/hot air and microscope",False,False
C403,10n / 50V X7R / 10%,TDK,C1608X7R1H103K080AA,1,1,manual,C_0603_1608Metric,top,6.9,32.299999,0.0,"manual assembly after factory inspection, using iron/hot air and microscope",False,False
C404,1u / 16V X7R / 10%,KEMET / YAGEO,C0603C105K4RACTU,1,1,manual,C_0603_1608Metric,top,12.6,33.0,0.0,"manual assembly after factory inspection, using iron/hot air and microscope",False,False
C405,10n / 50V X7R / 10%,TDK,C1608X7R1H103K080AA,1,1,manual,C_0603_1608Metric,top,12.6,34.6,0.0,"manual assembly after factory inspection, using iron/hot air and microscope",False,False
C406,10n / 50V X7R / 10%,TDK,C1608X7R1H103K080AA,1,1,manual,C_0603_1608Metric,top,10.2,33.0,90.0,"manual assembly after factory inspection, using iron/hot air and microscope",False,False
C407,100n / 50V X7R / 10%,TDK,C1608X7R1H104K080AA,1,1,manual,C_0603_1608Metric,top,10.95,28.5,0.0,"manual assembly after factory inspection, using iron/hot air and microscope",False,False
C408,1u / 16V X7R / 10%,KEMET / YAGEO,C0603C105K4RACTU,1,1,manual,C_0603_1608Metric,top,14.15,28.5,0.0,"manual assembly after factory inspection, using iron/hot air and microscope",False,False
C409,1u / 16V X7R / 10%,KEMET / YAGEO,C0603C105K4RACTU,1,1,manual,C_0603_1608Metric,top,9.1,36.3,0.0,"manual assembly after factory inspection, using iron/hot air and microscope",False,False
C501,4.7u / 16V X5R / 10%,TDK,C1608X5R1C475K080AC,1,1,manual,C_0603_1608Metric,top,4.0,42.7,0.0,"manual assembly after factory inspection, using iron/hot air and microscope",False,False
C502,4.7u / 16V X5R / 10%,TDK,C1608X5R1C475K080AC,1,1,manual,C_0603_1608Metric,top,4.0,48.7,0.0,"manual assembly after factory inspection, using iron/hot air and microscope",False,False
C504,100n / 50V X7R / 10%,TDK,C1608X7R1H104K080AA,1,1,manual,C_0603_1608Metric,top,8.5,48.1,0.0,"manual assembly after factory inspection, using iron/hot air and microscope",False,False
C505,1u / 16V X7R / 10%,KEMET / YAGEO,C0603C105K4RACTU,1,1,manual,C_0603_1608Metric,top,9.2,51.5,90.0,"manual assembly after factory inspection, using iron/hot air and microscope",False,False
C506,10n / 50V X7R / 10%,TDK,C1608X7R1H103K080AA,1,1,manual,C_0603_1608Metric,top,16.649999,34.025,90.0,"manual assembly after factory inspection, using iron/hot air and microscope",False,False
C507,10n / 50V X7R / 10%,TDK,C1608X7R1H103K080AA,1,1,manual,C_0603_1608Metric,top,6.65,38.1,90.0,"manual assembly after factory inspection, using iron/hot air and microscope",False,False
C508,100n / 50V X7R / 10%,TDK,C1608X7R1H104K080AA,1,1,manual,C_0603_1608Metric,top,15.5,38.4,0.0,"manual assembly after factory inspection, using iron/hot air and microscope",False,False
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
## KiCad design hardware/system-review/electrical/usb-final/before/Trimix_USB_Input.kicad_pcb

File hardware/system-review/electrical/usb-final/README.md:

# USB daughterboard engineering completion

The USB circuit and routing are complete for integration review. **Fabrication is held.**
The native board retains the original GCT recommended copper lands and exact
cutout/connector pose. Its full manufacturing DRC deliberately exposes the
source geometry conflicts; no exception converts those findings into a pass.

## What changed

The obsolete two-wire PCB and two local 5.1 kΩ CC resistors were replaced with
a six-wire harness and the two protection ICs. J902 maps directly to main J101:
1 USB_5V, 2 GND, 3 CC1, 4 CC2, 5 D+, 6 D−. The main TUSB320LAI provides Rd;
D+/D− serve main-board BC1.2 detection. This is a nominal 5 V power input,
not a high-speed USB data interface or a USB-PD voltage negotiator.

U901 is TI TPD4E05U06DQAR. Pads 1, 2, 4 and 5 protect CC1, CC2, D+ and D−;
3/8 are ground. The PCB explicitly bridges 1–10, 2–9, 4–7 and 5–6 with copper
under the package. TI permits this optional use of NC lands; no internal
pass-through is assumed. D901 is TPD1E10B06DYAR: pad 1 VBUS, pad 2 GND.
[TI TPD4E05U06 Rev O](https://www.ti.com/lit/ds/symlink/tpd4e05u06.pdf),
[TI TPD1E10B06 Rev G](https://www.ti.com/lit/ds/symlink/tpd1e10b06.pdf).

U901 uses the DQA0010B land example (4230307/A): 0.835 mm row pitch,
0.5 mm lead pitch, 0.565 × 0.20 mm signal lands and joined 3/8 ground metal.
The optional centre via is omitted; the ground connection reaches an external
via. D901 uses the DYA0002A example (4224978/B), 0.67 × 0.40 mm lands on
1.48 mm centres. Confirm the quoted DQA package/stencil variant with the
assembler; two DQA variants appear in the datasheet.

There are 94 track segments and 14 vias. Signal copper is 0.15 mm wide with
0.15 mm minimum clearance. VBUS trunks are 0.60 mm; their 0.09 mm pad escapes
are 0.30 mm wide. D901 is a shunt, so its 0.30 mm branch does not form a series
bottleneck for normal input current. Both layers have ground copper, and the
ESD ground paths use short external vias. The D901 ground land to via distance
is 0.51 mm. U901's ground return uses the external 3/8 bridge and a 0.7825 mm
trace from pad 8 to its via. These dimensions do not establish transient loop
inductance or assembled-port discharge performance. Source-current limiting
and overvoltage coordination belong to the separately reviewed main board.

## Verification and fabrication holds

Final native ERC: **0 violations**. Native PCB check: **0 unconnected items,
0 schematic parity issues**, with **22 manufacturing violations retained**:
20 copper-edge instances and 2 PTH annular-width instances. Some connector
pad aliases share physical copper and are counted separately by KiCad.
All remaining violations concern the unchanged GCT footprint/edge geometry.
There are no routing clearances, shorts, extra tracks crossing the edge,
co-located holes, silkscreen overlaps or unmapped schematic pins in that result.
See `usb-drc.json`, `usb-erc.json` and `audit.json`; DRC is not a physical test.

The current [JLCPCB published capabilities](https://jlcpcb.com/capabilities/pcb-capabilities/)
support the chosen 1 oz trace/space and via sizes. However, its ordinary routed
edge requirement is 0.20 mm, while the GCT lands give 0.10 mm at the SMT row and
0.15 mm at several ground lands. JLCPCB also gives a two-layer PTH minimum ring
of 0.18 mm, while the GCT two 0.80 mm lands with 0.50 mm holes give 0.15 mm.
Its quoted high-precision route tolerance is ±0.10 mm; the GCT recommended
layout gives ±0.05 mm. That mismatch requires a confirmed manufacturing
process. The TI 0.20 mm-wide signal lands also need explicit assembly/process
review against the generic pad-size line in the capability table. Panel tooling,
flat finish, stencil, reflow and inspection requirements must be agreed before
an order. The nominal board thickness requirement is independently satisfied
by 0.60 ±0.10 mm; that alone does not resolve the other conflicts.

The source [GCT Rev B drawing](https://gct.co/files/drawings/usb4720.pdf) is saved
unchanged at `hardware/cad/rev03/components/GCT_USB4720_RevB_drawing.pdf`.
A rearward SMT-land shift was considered but rejected because solder-tail
coverage and tolerance could not be proved from the available drawing. Moving
the rear cutout to one end of its tolerance consumes the available tolerance
and reduces the current CAD plastic clearance. Neither was accepted as a
fabrication fix. The rejected land trial is preserved only in `before/`.

**Required closure:** obtain manufacturer/assembler approval of a real alternate
land/cutout layout, or choose a supplier/process that explicitly accepts and
meets the original edge, annular, slot, placement and routing tolerances. A
compatible alternate connector would require a new mechanical design review.
No quote, order or outside message has been sent. `manufacturing-diagnostic/`
is labelled accordingly; those exports are for inspection, not release.

D901's surge clamp is not limited to 5.5 V. Its published clamping voltages can
exceed the downstream limiter's input rating, so device-level IEC specifications
cannot prove coordinated VBUS protection or a system ESD rating. Verify the
main-board protection chain and then measure the assembled port's hot-plug and
transient behaviour. No charger, connector or gas-analyser safety pass is made.

## Mechanical and STEP contract

No connector position, purchased component scale or board outline changed.
J901 remains at KiCad (108, 110.14) mm, 0°. J902 is the intended six-wire row
at (108, 104.5), giving pad centres X103.5…112.5 mm at 1.8 mm pitch.
The earlier two-pad board had J902 at (105.9,104.0); that obsolete pose was
replaced with the already approved six-wire/Fusion row.

| Part | KiCad XY mm | Rotation | Maximum purchased envelope |
| --- | --- | --- | --- |
| U901 | 109.5, 106.8 | 90° | 2.6 × 1.1 mm in installed XY; height 0.55 mm |
| D901 | 104.0, 108.0 | 0° | 1.70 mm terminal span × 1.15 mm conservative width including mould-flash allowance; height 0.77 mm |
| J902 | 108.0, 104.5 | 0° | Wires/solder/bends unmeasured; 4.5 mm above-board allowance is provisional |

For the established nominal Fusion PCB top Z25.5 and support underside Z31.2,
U901 reaches Z26.05 and D901 Z26.27 before solder/placement allowance. A separate
0.10 mm assembly allowance would give Z26.15 and Z26.37, respectively; it is
an engineering allowance, not a measured solder thickness. The provisional
harness allowance reaches Z30.0, but physical bends and solder tips must be
measured rather than treated as a guaranteed fit. The nominal PCB stack is
Z24.9…25.5 and the connector/factory stake reconstruction remains separate.

`Trimix_USB_Input.step` contains the PCB, copper and unchanged KiCad nominal
package models for U901/D901. The connector and harness remain separate native
Fusion assemblies so they are not duplicated. The STEP uses the drill origin
(100,100) with the KiCad Y sign convention. Existing Fusion registration is
X+34.5, Y+18 with the previous Z+24.945 translation; the CAD owner must confirm
actual exported face elevations when reimporting. `height-contract.json` records
source maxima separately from the illustrative models. The generic models have
nominal heights about 0.53 and 0.63 mm; those smaller visual bodies must not replace
the maximum envelope check. Existing KiCad model license notices are preserved.

## Main hierarchy handoff and reproducibility

The main-PCB owner can copy `USB_Input-integration.kicad_sch` to its existing
`USB_Input.kicad_sch`, preserving the checked hierarchy UUID/path. All four
USB parts are excluded from the main PCB and main-board purchasing quantities;
the separate USB BOM lists their quantities. Add local library aliases:

- `Trimix_USB` symbols: `${KIPRJMOD}/../usb-input/Trimix_USB.kicad_sym`
- `Trimix_USB` footprints: `${KIPRJMOD}/../usb-input/Trimix_USB.pretty`

Then regenerate the main XML/ERC/BOM and verify exclusion and hierarchy paths.
No main-PCB files or live MCP board state were edited by this task.

`before/` preserves the original USB project. `build_usb_final.py` builds its
local libraries and schematic; `autoroute_usb.py` constructs the USB board
using the frozen original outline. They run with the existing KiCad MCP Python
virtual environment as an **offline Python interpreter**, never a live MCP
board. After that process exits, run `configure_rules.py`, because SWIG retains
in-memory project settings that it saves with the board. Run native DRC with
zone refill/save before `export_usb.py`. `final_silkscreen.py` is the recorded
incremental marking adjustment; the builder now generates those dimensions.
`export-commands.json`/`export.log` contain exact export commands and statuses.

Top/bottom native renders and the schematic were visually reviewed. The PCB and
schematic were reopened by native CLI checks. STEP importer/clearance acceptance
is the CAD integration step, not an implied pass from exporting the file. Final
source and artifact hashes are bound by `audit.json`. Physical fit, solderability,
slot precision, insertion loads, strain relief, source orientation/detach, load
heating, hot plug, ESD and leakage/sealing checks remain pending.

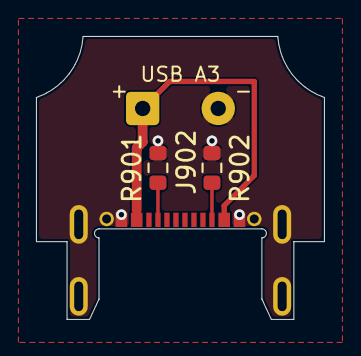
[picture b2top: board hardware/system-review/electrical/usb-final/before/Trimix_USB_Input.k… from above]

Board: 2 copper layers, 16.0 x 15.7 mm, 4 parts (0 on the bottom side), 4 nets.

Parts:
J901: GCT USB4720-03-A; USB_C_GCT_USB4720-03-A_A3
J902: TO MAIN PCB J101; SolderWire-0.25sqmm_1x02_P4.2mm_D0.65mm_OD1.7mm
R901, R902: 5.1k / 1%; R_0603_1608Metric

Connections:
GND: J901.A1, J901.A12, J901.B1, J901.B12, J901.SH, J902.2, R901.2, R902.2
USB_5V: J901.A4, J901.A9, J901.B4, J901.B9, J902.1
USB_CC1: J901.A5, R901.1
USB_CC2: J901.B5, R902.1
